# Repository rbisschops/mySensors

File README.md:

# mySensors
My personal [MySensors](http://mysensors.org) hardware and sofware projects.

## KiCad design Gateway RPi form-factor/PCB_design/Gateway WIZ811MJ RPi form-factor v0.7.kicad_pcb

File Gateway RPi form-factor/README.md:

# mySensors Gateway Raspberry Pi form-factor
mySensors Gateway Raspberry Pi form-factor

mySensors Ethernet Gateway in the same form-factor as a Raspberry Pi.

The development was done so I can fit it in a custom made cluster of RPi's using the same mountingholes and the same (5V) power supply)

For more info and dicussion on this project, visit the [mySensors forum thread ](https://sf.mysensors.org/topic/xxxx).

You can find the hardware design also on [openhardware.io](https://www.openhardware.io/view/xxxx)

External dependencies:
- KiCad schematics editor 
- Kicad Pcbnew

License:
[CERN Open Hardware Licence v1.2](http://ohwr.org/cernohl)

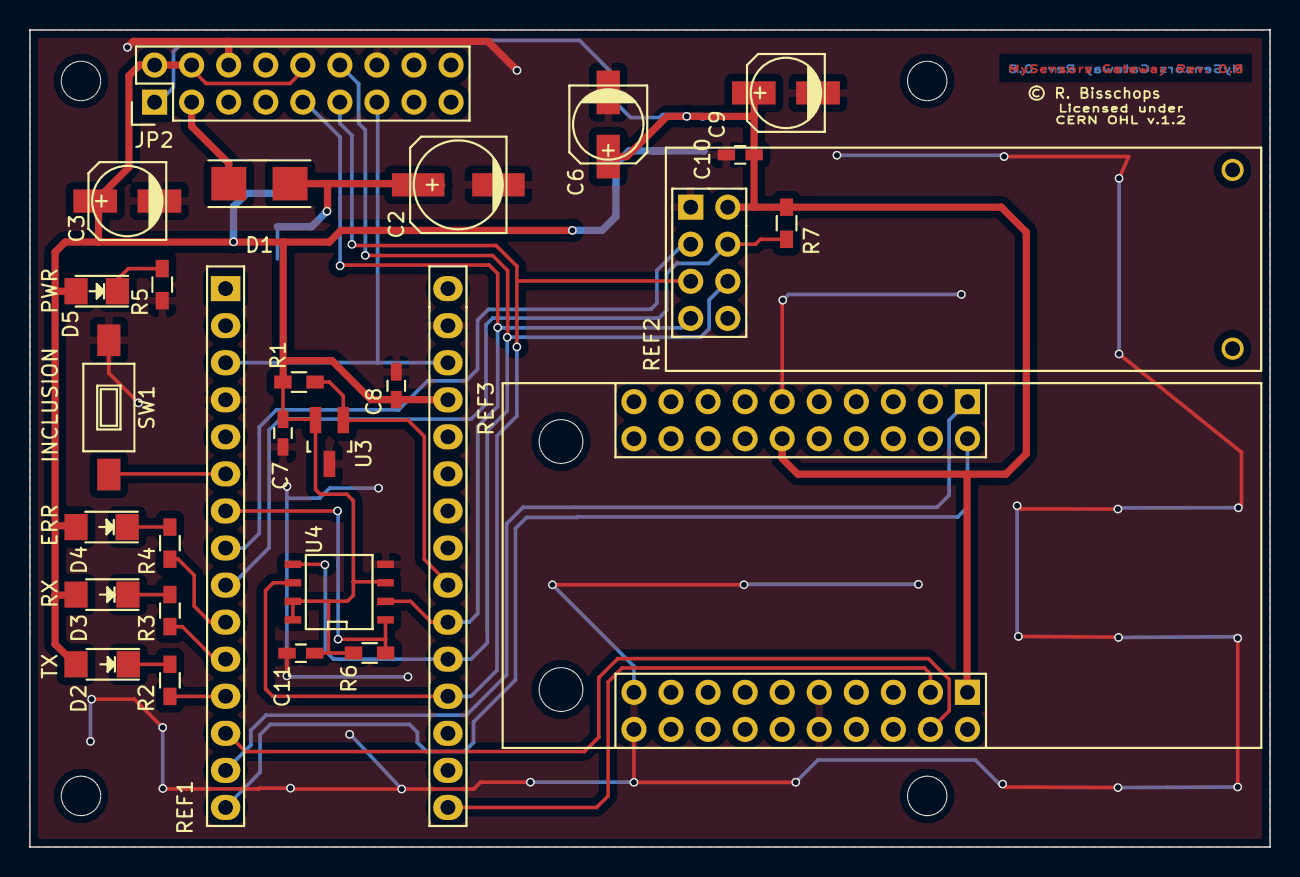
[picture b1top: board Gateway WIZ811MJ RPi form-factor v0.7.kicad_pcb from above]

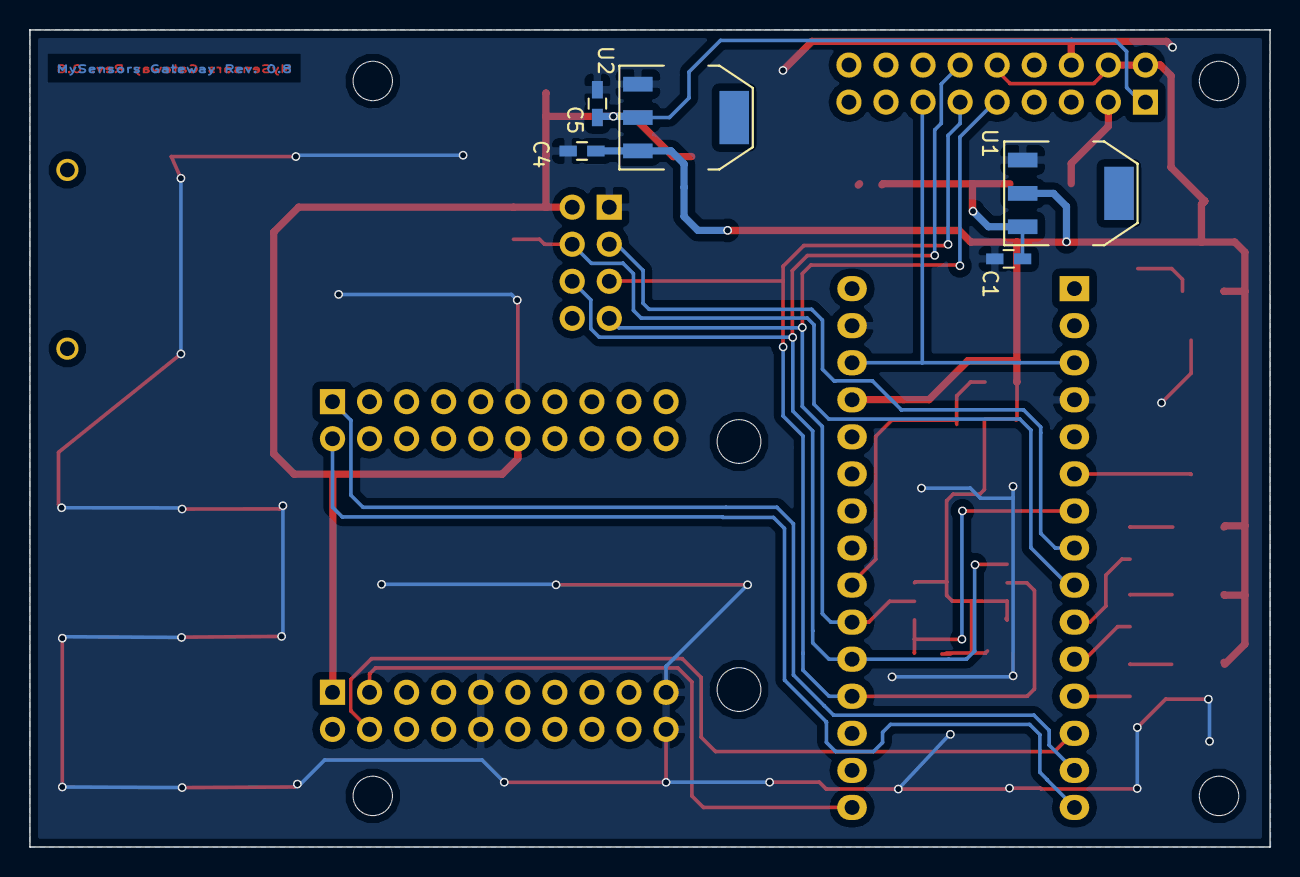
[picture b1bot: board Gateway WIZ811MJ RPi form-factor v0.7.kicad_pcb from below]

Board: 2 copper layers, 85.0 x 56.0 mm, 32 parts (5 on the bottom side), 25 nets.

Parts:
C1, C4, C5, C7, C8, C10, C11: 100nF; C_0603_HandSoldering
C2: 47uF; c_elec_6.3x5.3
C3, C6: 10uF; c_elec_5x5.3
C9: 4uF7; c_elec_5x5.3
D1: 1N4007 M7; DO-214AC
D2: TX; LED_1206
D3: RX; LED_1206
D4: ERR; LED_1206
D5: PWR; LED_1206
JP2: CONN_02x9; Socket_Strip_Straight_2x09_mirrored
R1, R7: 56K; R_0603_HandSoldering
R2, R3, R4, R5: 1K; R_0603_HandSoldering
R6: 4K7; R_0603_HandSoldering
REF1: Arduino_Nano
REF2: NRF24L01; NRF24L01_PA_LNA
REF3: WIZ811MJ
SW1: SW_PUSH; SW_SPST_FSMSM
U1: AP1117E50; SOT-223
U2: AP1117D33; SOT-223
U3: ATSHA240A; SOT-23_Handsoldering
U4: AT25DF512C; SOIC-8-N

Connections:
+3.3V: C5.1, C6.1, C9.1, C10.1, JP2.1, R7.1, REF2.2, REF3.112, REF3.201, U2.2
ETH-MISO: REF1.15, REF3.102
ETH-MOSI: REF1.14, REF3.101
ETH-NSS: REF1.13, REF3.204
ETH-SCK: REF1.16, REF3.203
FLASH_CSN: R6.2, REF1.7, U4.1
GND: C1.2, C2.2, C3.2, C4.2, C5.2, C6.2, C7.2, C8.2, C9.2, C10.2, C11.2, JP2.6, JP2.14, R5.2, REF1.4, REF1.29, REF2.1, REF3.111, REF3.209, REF3.210, REF3.219, REF3.220, SW1.1, U1.1, U2.1, U3.3, U4.4
MISO: JP2.9, REF1.21, REF2.7, U4.2
MOSI: JP2.12, REF1.20, REF2.6, U4.5
unnamed: C1.1, C2.1, D1.1, U1.3
unnamed: D2.1, R2.1
unnamed: D3.1, R3.1
unnamed: D4.1, R4.1
unnamed: D5.1, R5.1
unnamed: REF1.6, SW1.2
PWR: D1.2, JP2.3
RAD-CE: REF1.8, REF2.3
RAD-CSN: R7.2, REF1.9, REF2.4
RAD-ERR: R4.2, REF1.10
RAD-RX: R3.2, REF1.11
RAD-TX: R2.2, REF1.12
RESET: JP2.13, REF1.3, REF1.28
SCK: JP2.11, REF1.19, REF2.5, U4.6
SEC-SDA: R1.2, REF1.22, U3.1
VCC: C3.1, C4.1, C7.1, C8.1, C11.1, D2.2, D3.2, D4.2, D5.2, JP2.2, JP2.4, JP2.10, R1.1, R6.1, REF1.27, U1.2, U2.3, U3.2, U4.3, U4.7, U4.8

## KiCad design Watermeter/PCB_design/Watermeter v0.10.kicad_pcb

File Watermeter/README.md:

# mySensors Watermeter
mySensors Watermeter

Adapted mySensors Arduino sketch for measuring pulses on a (standard) household watermeter.

The development was initially done for a Itron Aquadis+ watermeter, but can be adapted for any other watermeter that has the ability to read one of the rotating counters externally.

For more info and dicussion on this project, visit the [mySensors forum thread ](https://sf.mysensors.org/topic/2816/itron-aquadis-watermeter-sensor).

You can find the hardware design also on [openhardware.io](https://www.openhardware.io/view/15/Itron-Aquadis-watermeter-sensor)

External dependencies:
- KiCad schematics editor 
- Kicad Pcbnew

License:
[CERN Open Hardware Licence v1.2](http://ohwr.org/cernohl)

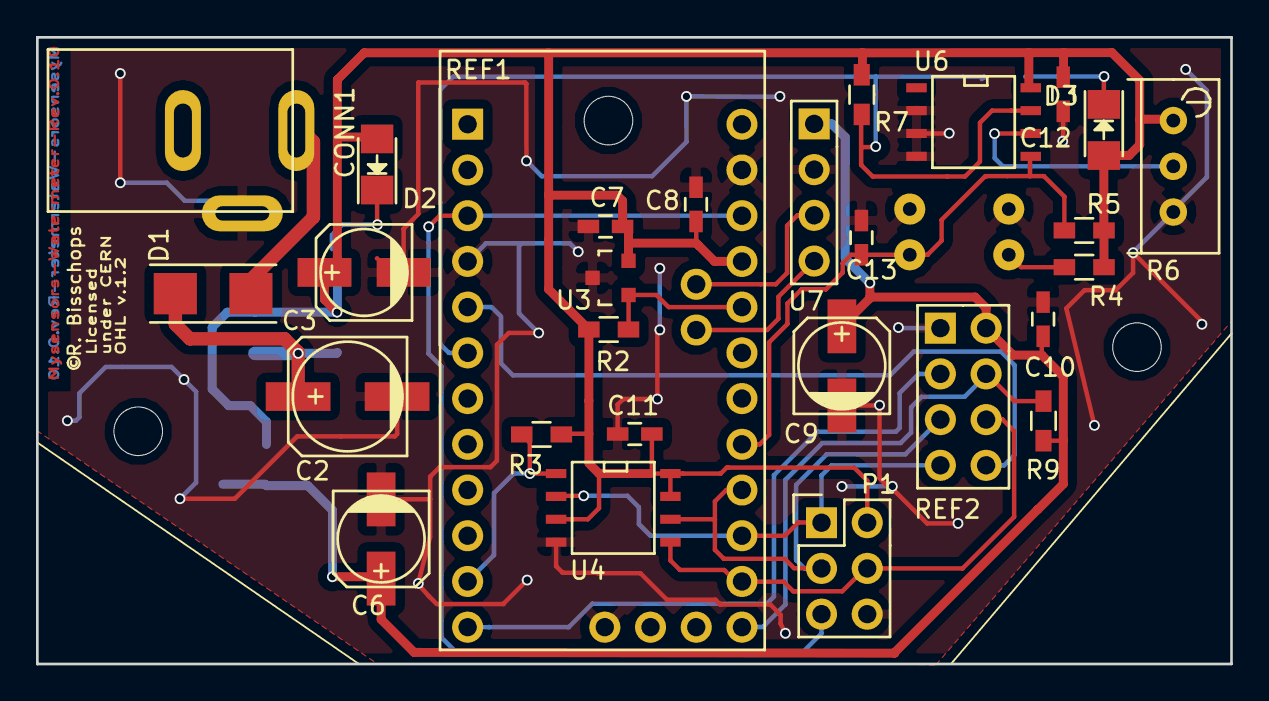
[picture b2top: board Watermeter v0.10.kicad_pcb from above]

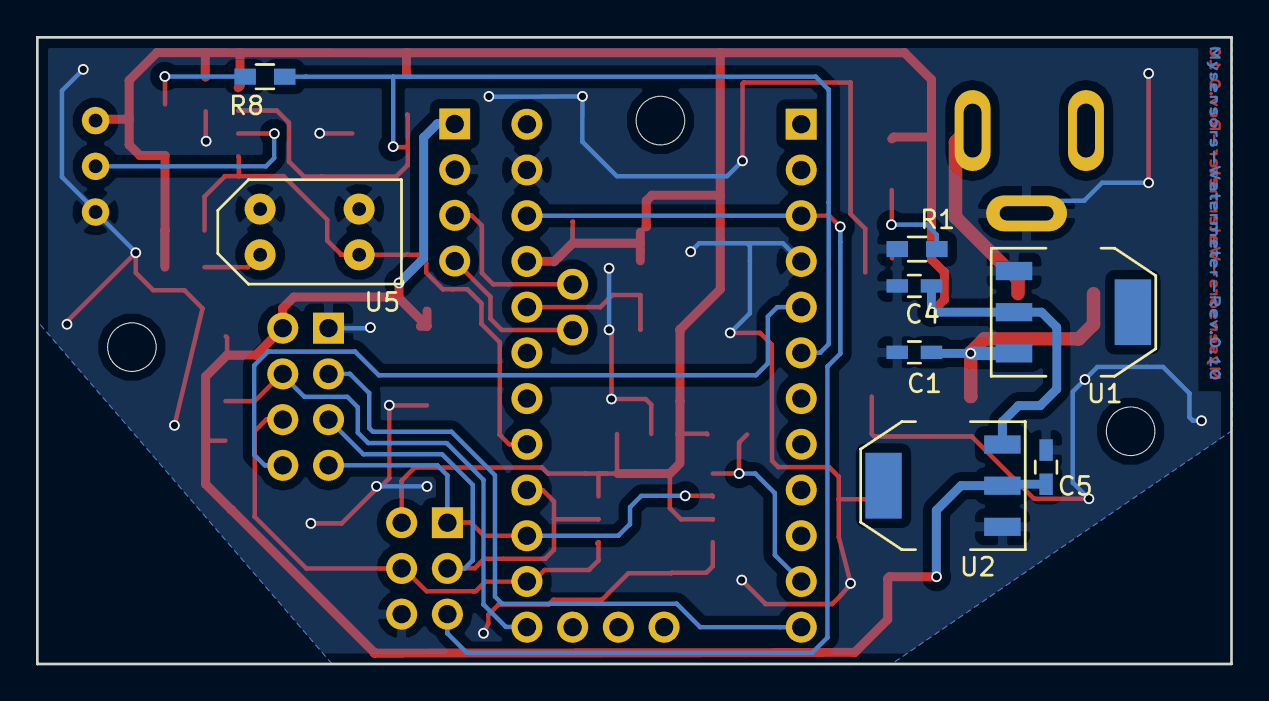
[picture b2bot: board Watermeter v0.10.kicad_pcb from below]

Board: 2 copper layers, 66.3 x 34.8 mm, 36 parts (8 on the bottom side), 22 nets.

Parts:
C1, C4, C5, C7, C8, C10, C11, C12, C13: 100nF; C_0603_HandSoldering
C2: 47uF; c_elec_6.3x5.3
C3, C6: 10uF; c_elec_5x5.3
C9: 4u7; c_elec_5x5.3
CONN1: CONN_01X02; Socket_Jack_5.5-2.1MM
D1: 1N4007 M7; DO-214AC
D2: PWR; LED_1206
D3: PULSE; LED_1206
P1: CONN_02X03; Pin_Header_Straight_2x03
R1, R8: 1K; R_0603_HandSoldering
R2, R3, R9: 56K; R_0603_HandSoldering
R4: 180; R_0603_HandSoldering
R5, R7: 10K; R_0603_HandSoldering
R6: 10K; Potentiometer_Custom_Inline_ScrewUp
REF1: Arduino_Mini_Pro 5V; Arduino_Pro_Mini_non_FTDI
REF2: NRF24L01; NRF24L01_STD
U1: AP1117D50; SOT-223
U2: AP1117D33; SOT-223
U3: ATSHA240A; SOT-23
U4: AT25DF512C; SOIC-8-N
U5: TCRT5000
U6: LM393; SOIC-8-N
U7: SI7021

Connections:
+3.3V: C5.1, C6.1, C9.1, C10.1, R9.1, REF2.2, U2.2, U7.1
A0: C13.1, R5.2, REF1.17, U5.3, U6.5
D3: R7.2, R8.2, REF1.6, U6.7
FLASH-CSN: R3.2, REF1.11, U4.1
GND: C1.2, C2.2, C3.2, C4.2, C5.2, C6.2, C7.2, C8.2, C9.2, C10.2, C11.2, C12.2, C13.2, CONN1.1, P1.6, R1.2, R6.3, REF1.4, REF1.23, REF1.35, REF2.1, U1.1, U2.1, U3.3, U4.4, U5.2, U5.4, U6.2, U6.3, U6.4, U7.2
MISO: P1.1, REF1.15, REF2.7, U4.2
MOSI: P1.4, REF1.14, REF2.6, U4.5
unnamed: C1.1, C2.1, D1.1, U1.3
unnamed: CONN1.2, D1.2
unnamed: D2.1, R1.1
unnamed: D3.1, R8.1
unnamed: R4.2, U5.1
unnamed: R6.2, U6.6
RAD_CE: REF1.12, REF2.3
RAD_CSN: R9.2, REF1.13, REF2.4
RAD_IRQ: REF1.5, REF2.8
RESET: P1.5, REF1.3, REF1.22
SCK: P1.3, REF1.16, REF2.5, U4.6
SEC-SDA: R2.2, REF1.20, U3.1
TMP_SCL: REF1.32, U7.3
TMP_SDA: REF1.31, U7.4
VCC: C3.1, C4.1, C7.1, C8.1, C11.1, C12.1, D2.2, D3.2, P1.2, R2.1, R3.1, R4.1, R5.1, R6.1, R7.1, REF1.21, U1.2, U2.3, U3.2, U4.3, U4.7, U4.8, U6.8

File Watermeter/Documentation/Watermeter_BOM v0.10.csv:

Id;Designator;Package/Footprint;Qty;Value;Supplier ;Supplier ref.
1;R1;0603;1;1K;Aliexpress;0603 SMD Resistor Kit 1% 10ohm to 910Kohm
2;R2,R3;0603;2;56K;Aliexpress;0603 SMD Resistor Kit 1% 10ohm to 910Kohm
3;R4;0603;1;180;Aliexpress;0603 SMD Resistor Kit 1% 10ohm to 910Kohm
4;R5,R7;0603;2;10K;Aliexpress;0603 SMD Resistor Kit 1% 10ohm to 910Kohm
5;R6;Potentiometer Custom Inline ScrewUp;1;10K;Aliexpress;10k Ohm 3296W Potentiometer Trim Trimmer Variable Resistor 25 Turn Pot
6;R8;0603;2;1K;Aliexpress;0603 SMD Resistor Kit 1% 10ohm to 910Kohm
7;C1,C4,C5,C7,C8,C10,C11,C12,C13;0603;9;100nF;Aliexpress;100nF X7R Error 10% 50V 0603 SMD Thick Film Chip Multilayer Ceramic Capacitor
8;C2;6.3x5.3;1;47uF;Aliexpress;47uF-35V-6-3-5-4-SMD-aluminum-Electrolytic capacitor
9;C3,C6;5x5.3;2;10uF;Aliexpress;25V 10UF SMD 4x5.4mm chip Aluminum-Electrolytic capacitor
10;C9;5x5.3;1;4u7;Aliexpress;16V-4-7UF-SMD-4x5mm-Aluminum-Electrolytic capacitor
11;D1;DO-214AC;1;1N4007 M7;Aliexpress; SMD 1N4007 Rectifier Diode 1A 1000V M7 Original
12;D2;1206;1;SMD LED;Aliexpress;1206-SMD-White-Red-Blue-Green-Yellow Super-Bright
13;D3;1206;1;SMD LED;Aliexpress;1206-SMD-White-Red-Blue-Green-Yellow Super-Bright
14;U1;SOT-223;1;AP1117D50;Aliexpress;AMS1117-5.0 SOT-223 5 V Lineaire Regulator LM1117
15;U2;SOT-223;1;AP1117D33;Aliexpress;AMS1117-3.3 SOT-223 3.3 V Lineaire Regulator LM1117
16;U3;SOT-23;1;ATSHA240A;Digi-Key;Atmel ATSHA204A-STUCZ-T : Partnr: ATSHA204A-STUCZ-TCT-ND
17;U4;SOIC-8-N;1;AT25DF512C;Digi-Key;Adesto Technologies AT25DF512C-SSHN-B : Partnr: 1265-1179-5-ND
18;U5;TCRT5000;1;TCRT5000;Aliexpress;TCRT5000L TCRT5000 Reflective Infrared Optical Sensor Photoelectric Switche
19;U6;SOIC-8-N;1;LM393;Aliexpress;LM393DR-LM393-SOP-8-TI
20;U7;Header 1x4 pin;1;CONN_01X04;Aliexpress;Single Row Straight Female Pin Header Connector Strip for Arduino High Quality 2.54mm Black OH
21;REF1;Module;2;CONN_01X12 + CONN_01x02;Aliexpress;Single Row Straight Female Pin Header Connector Strip for Arduino High Quality 2.54mm Black OH
22;REF2;Header 2x4 pin;1;NRF24L01;Aliexpress;2x4 Pin 8P 2.54mm Double Row Female Straight Header Pitch
23;CONN1;Socket Jack5.5/2.1MM;1;CONN_01X02;Aliexpress;3 Pin DC Power Socket Jack DC005 5.5-2.1MM DC Power Interface Outlet
24;P1;Header 2x3 pin;1;CONN_02X03;Aliexpress;2.54mm 2x40 Pin Male Double Row Pin Header Strip
25;NRF24L01;Module;1;NRF24L01;Aliexpress;NRF24L01 2.4GHz Wireless Transceiver Module - Black
26;Arduino_Mini_Pro 5V;Module;1;Arduino_Mini_Pro 5V;Aliexpress;ATMEGA328P Pro Mini 328 Mini ATMEGA328 5V/16MHz for Arduino
27;SI7021;Module;1;SI7021;Aliexpress;Industrial High Precision Si7021 Humidity Sensor with I2C Interface for Arduino

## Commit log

2016-01-11 Updated description of the project
2016-01-13 Version 0.3 development version
2016-01-13 Watermeter sketch 3.0
2016-01-13 Watermeter sketch
2016-01-13 Added DXF of baseplate
2016-01-14 Setup watermeter for github in dev branch
2016-01-14 Updated due to error in VS
2016-01-14 Updated license
2016-01-15 small corrections
2016-01-15 small corrections and new forum link
2016-01-21 PCB board corrections after check Added optional SI7021 tem/hum sensor on PCB
2016-01-22 Removed old versions of PCB
2016-02-27 Multiple fixes in the pcb layout. Changed housing layouts.
2016-02-28 Added license documents and put licence notice on pcb. No board version change
2016-03-02 Changes to schematics. Added andchanged components
2016-03-02 Added PDF schematics for V0.10
2016-03-03 Added Gateway designs. Updated licence text
2017-12-26 Updated Arduino file for MySensors V2.x

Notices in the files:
Gateway RPi form-factor/PCB_design/Gateway WIZ811MJ RPi form-factor v0.7.kicad_pcb:
© R. Bisschops
Licensed under
CERN OHL v.1.2
